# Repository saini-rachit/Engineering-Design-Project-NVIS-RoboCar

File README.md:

# Engineering-Design-Project-NVIS-RoboCar
Engineering Design Project (UTA030) - Developed a Robocar (Buggy) to be operated remotely and follow the challenge instructions. Applied fundamentals of Analog Electronics, Sensors &amp; IOT and Electrical &amp; Electronics Engineering. 
Software Used: AutoDesk EAGLE CAD

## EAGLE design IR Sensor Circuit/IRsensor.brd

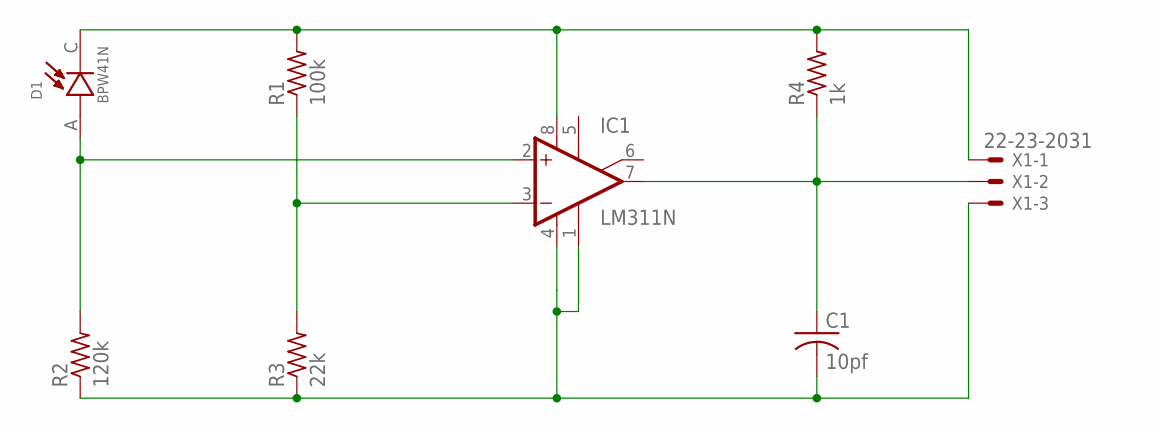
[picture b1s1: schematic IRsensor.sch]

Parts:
C1: 10pf; C025-024X044
D1: BPW41N; DIO_BPW41N
IC1: LM311N; DIL08
R1: 100k; 0204/5
R2: 120k; 0204/5
R3: 22k; 0204/5
R4: 1k; 0204/5
X1: 22-23-2031

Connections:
unnamed: C1.1, IC1.7 (OUT), R4.1, X1.2
unnamed: IC1.3 (-IN), R1.1, R3.2
unnamed: D1.A, IC1.2 (+IN), R2.2
unnamed: D1.C, IC1.8 (V+), R1.2, R4.2, X1.1
unnamed: C1.2, IC1.1 (GND), IC1.4 (V-), R2.1, R3.1, X1.3

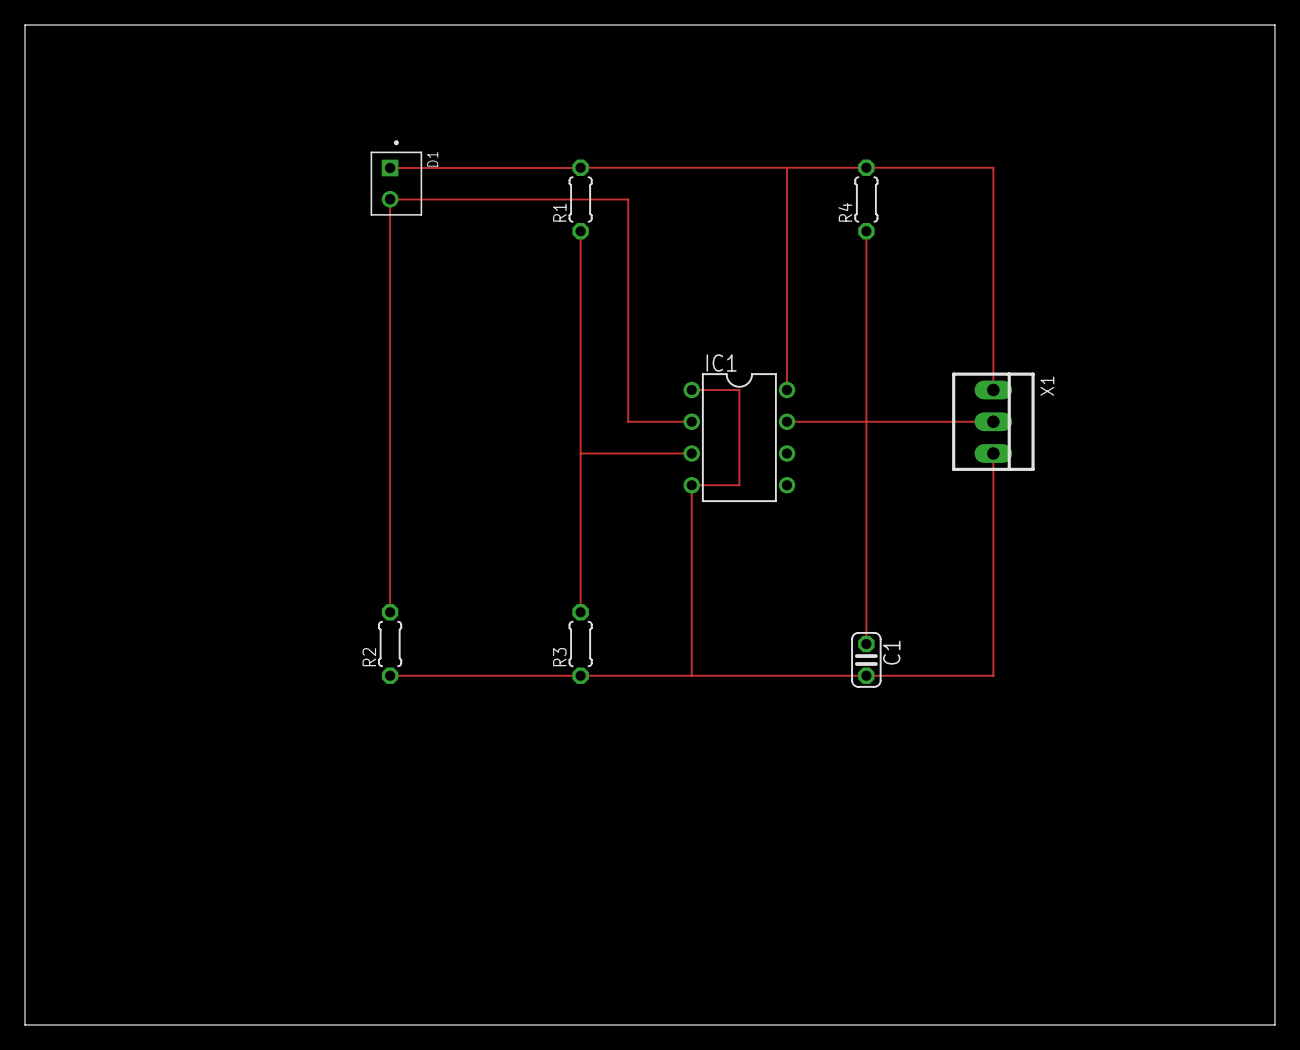
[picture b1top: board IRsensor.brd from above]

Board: 2 copper layers, 100.0 x 80.0 mm, 8 parts (0 on the bottom side), 5 nets.

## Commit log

2026-01-20 Include software used in project description
    Added software used for the project.
2026-01-22 Create IR Sensor Circuit
2026-01-22 Add files via upload
    Open the files ".brd" and ".sch" in AutoDesk Eagle CAD.
